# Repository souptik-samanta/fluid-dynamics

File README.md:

---
name: "Souptik Samanta"
slack_handle: "@Souptik Samanta"
github_handle: "@souptik-samanta"
tutorial: #no
wokwi: https://wokwi.com/projects/429317036413027329
---

# FLuid Dynamics

Wokwi link: https://wokwi.com/projects/429317036413027329

Led matrix pcb with rp2040 embeded into pcb to simulate fuild behavours based on inbuilt imu 

(pls include rough pricing of any extra components you're using 

| QTY  | PART                              | Approx Price | LCSC        |
|-----:|:----------------------------------|-------------:|:------------|
| 1    | IS31FL3741A-QFLS4-TR - 900Hz~29kHz 2.7V~5.5V QFN-60-EP(7x7) LED Drivers ICs ROHS | $2.89       | C2940604   |
| 5    | XDBS-CR2032-5 - Through Hole Blade Type Power Connector Assemblies ROHS | $0.30       | C48687404   |
| 2    | W25Q128JVSIQ - 128Mbit 2.7V~3.6V 133MHz SPI SOIC-8-208mil Memory (ICs) ROHS | $2.17       | C97521   |
| 5    | AMS1117-3.3 - 72dB@(120Hz) Positive SOT-223 Voltage Regulators - Linear, Low Drop Out (LDO) Regulators ROHS | $0.84       | C6186   |
| 1    | RP2040 - 133MHz LQFN-56(7x7) Microcontrollers ROHS | $1.14       | C2040   |
| 10   | SRV05-4 - 5A 75W 12.5V 6V Unidirectional SOT-23-6L TVS Diodes ROHS | $0.84       | C7420376   |
| 100  | FRC1206F2002TS - 250mW 20kΩ 200V ±100ppm/℃ Thick Film Resistor ±1% 1206 Chip Resistor - Surface Mount ROHS | $0.29       | C2933636   |
| 100  | 0402WGF274JTCE - 27.4Ω 62.5mW 50V ±100ppm/℃ Thick Film Resistor ±1% 0402 Chip Resistor - Surface Mount ROHS | $0.06       | C31439   |
| 100  | 0402WGF5101TCE - 5.1kΩ 62.5mW 50V ±100ppm/℃ Thick Film Resistor ±1% 0402 Chip Resistor - Surface Mount ROHS | $0.05       | C25905   |
| 100  | 0402WGF1001TCE - 1kΩ 62.5mW 50V ±100ppm/℃ Thick Film Resistor ±1% 0402 Chip Resistor - Surface Mount ROHS | $0.06       | C11702   |

final all toal is 20 - 25$ for parts  more parts on https://docs.google.com/spreadsheets/d/1B7IjNo7W825W_gv3a4BfWUKZrWtPnMB5DJiVofmm6nU/edit?usp=sharing

eh pretty easy

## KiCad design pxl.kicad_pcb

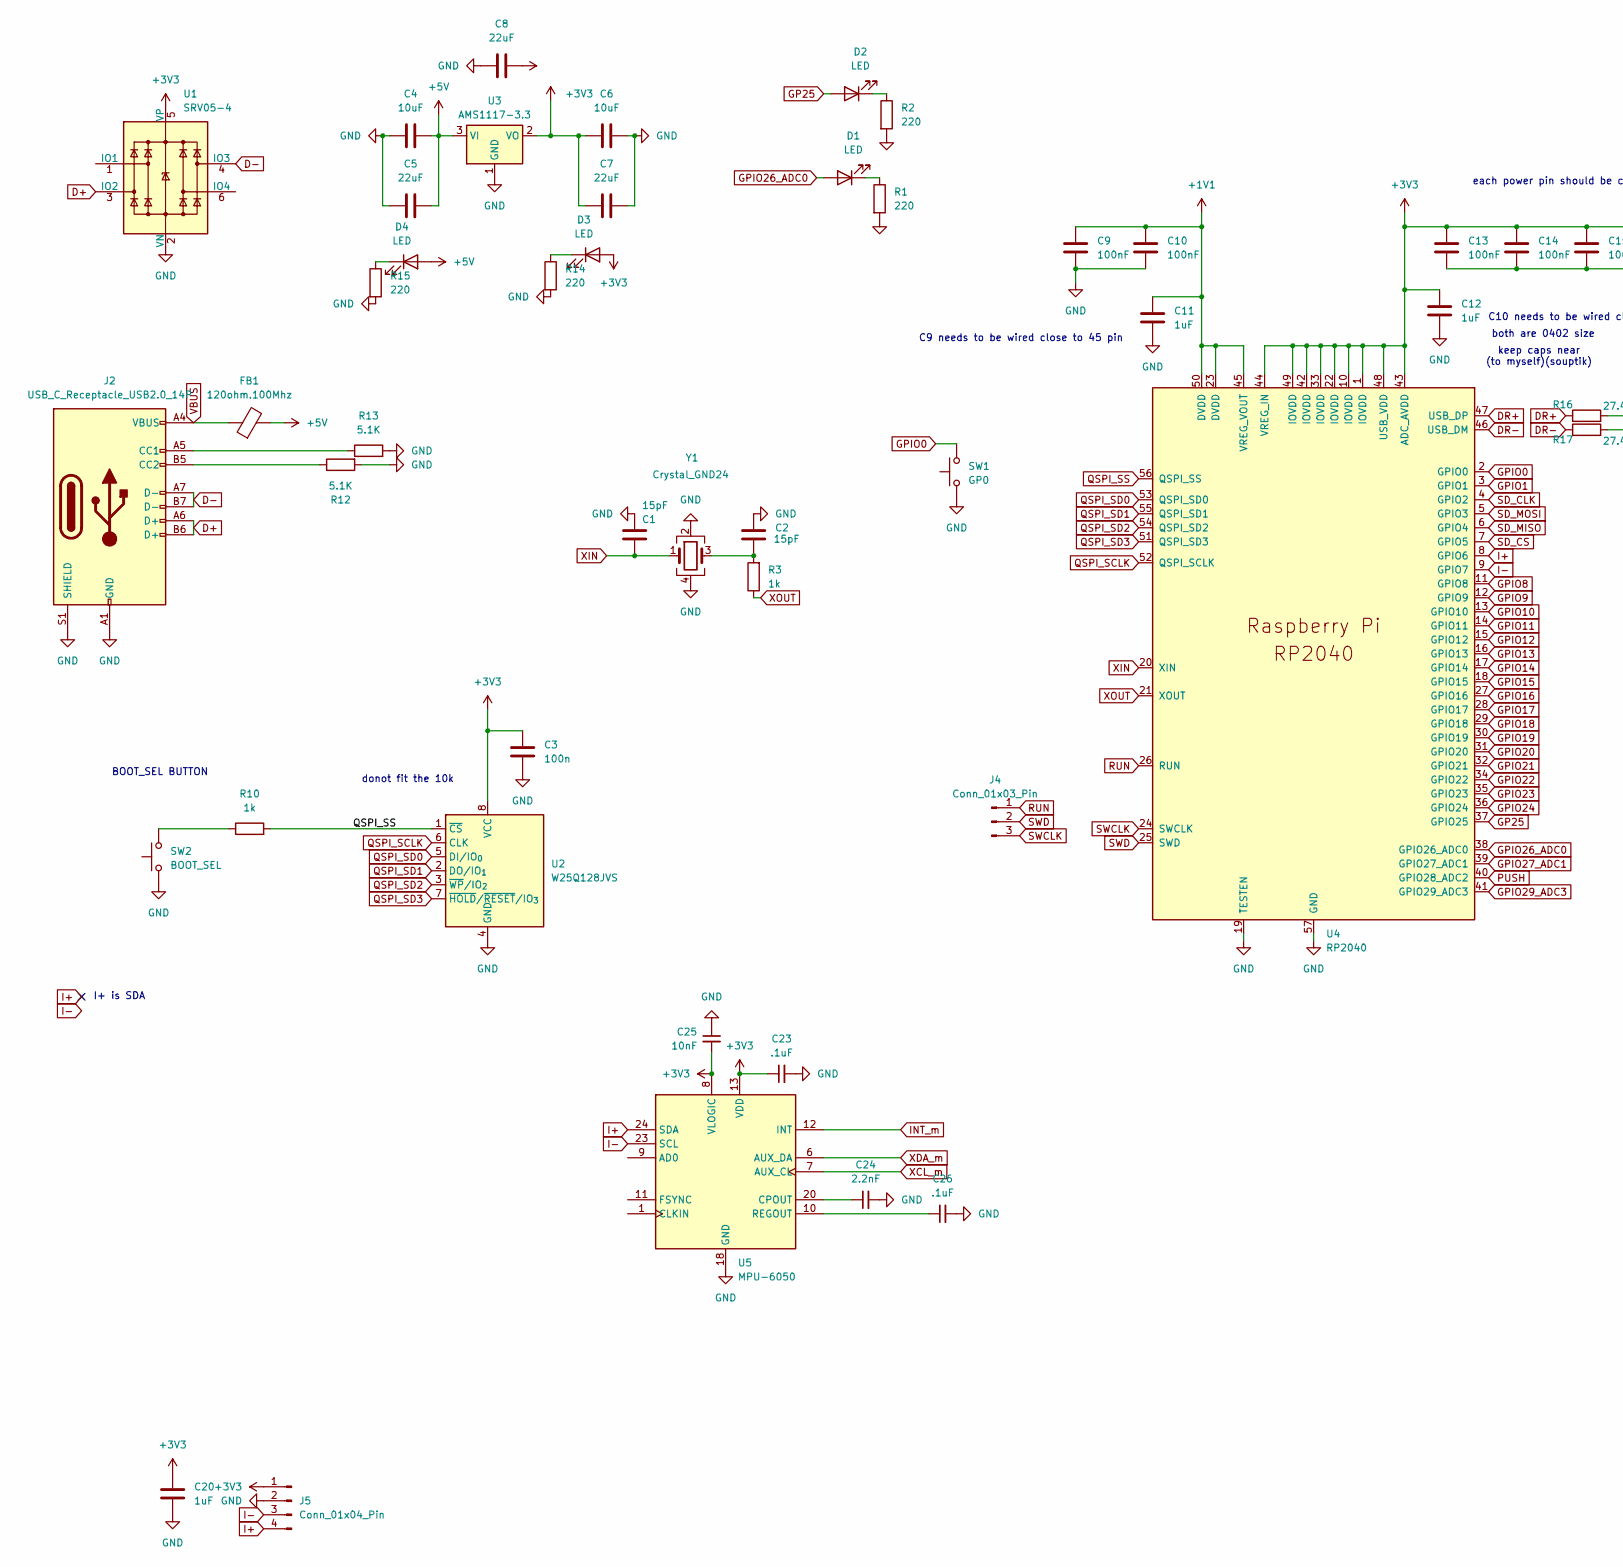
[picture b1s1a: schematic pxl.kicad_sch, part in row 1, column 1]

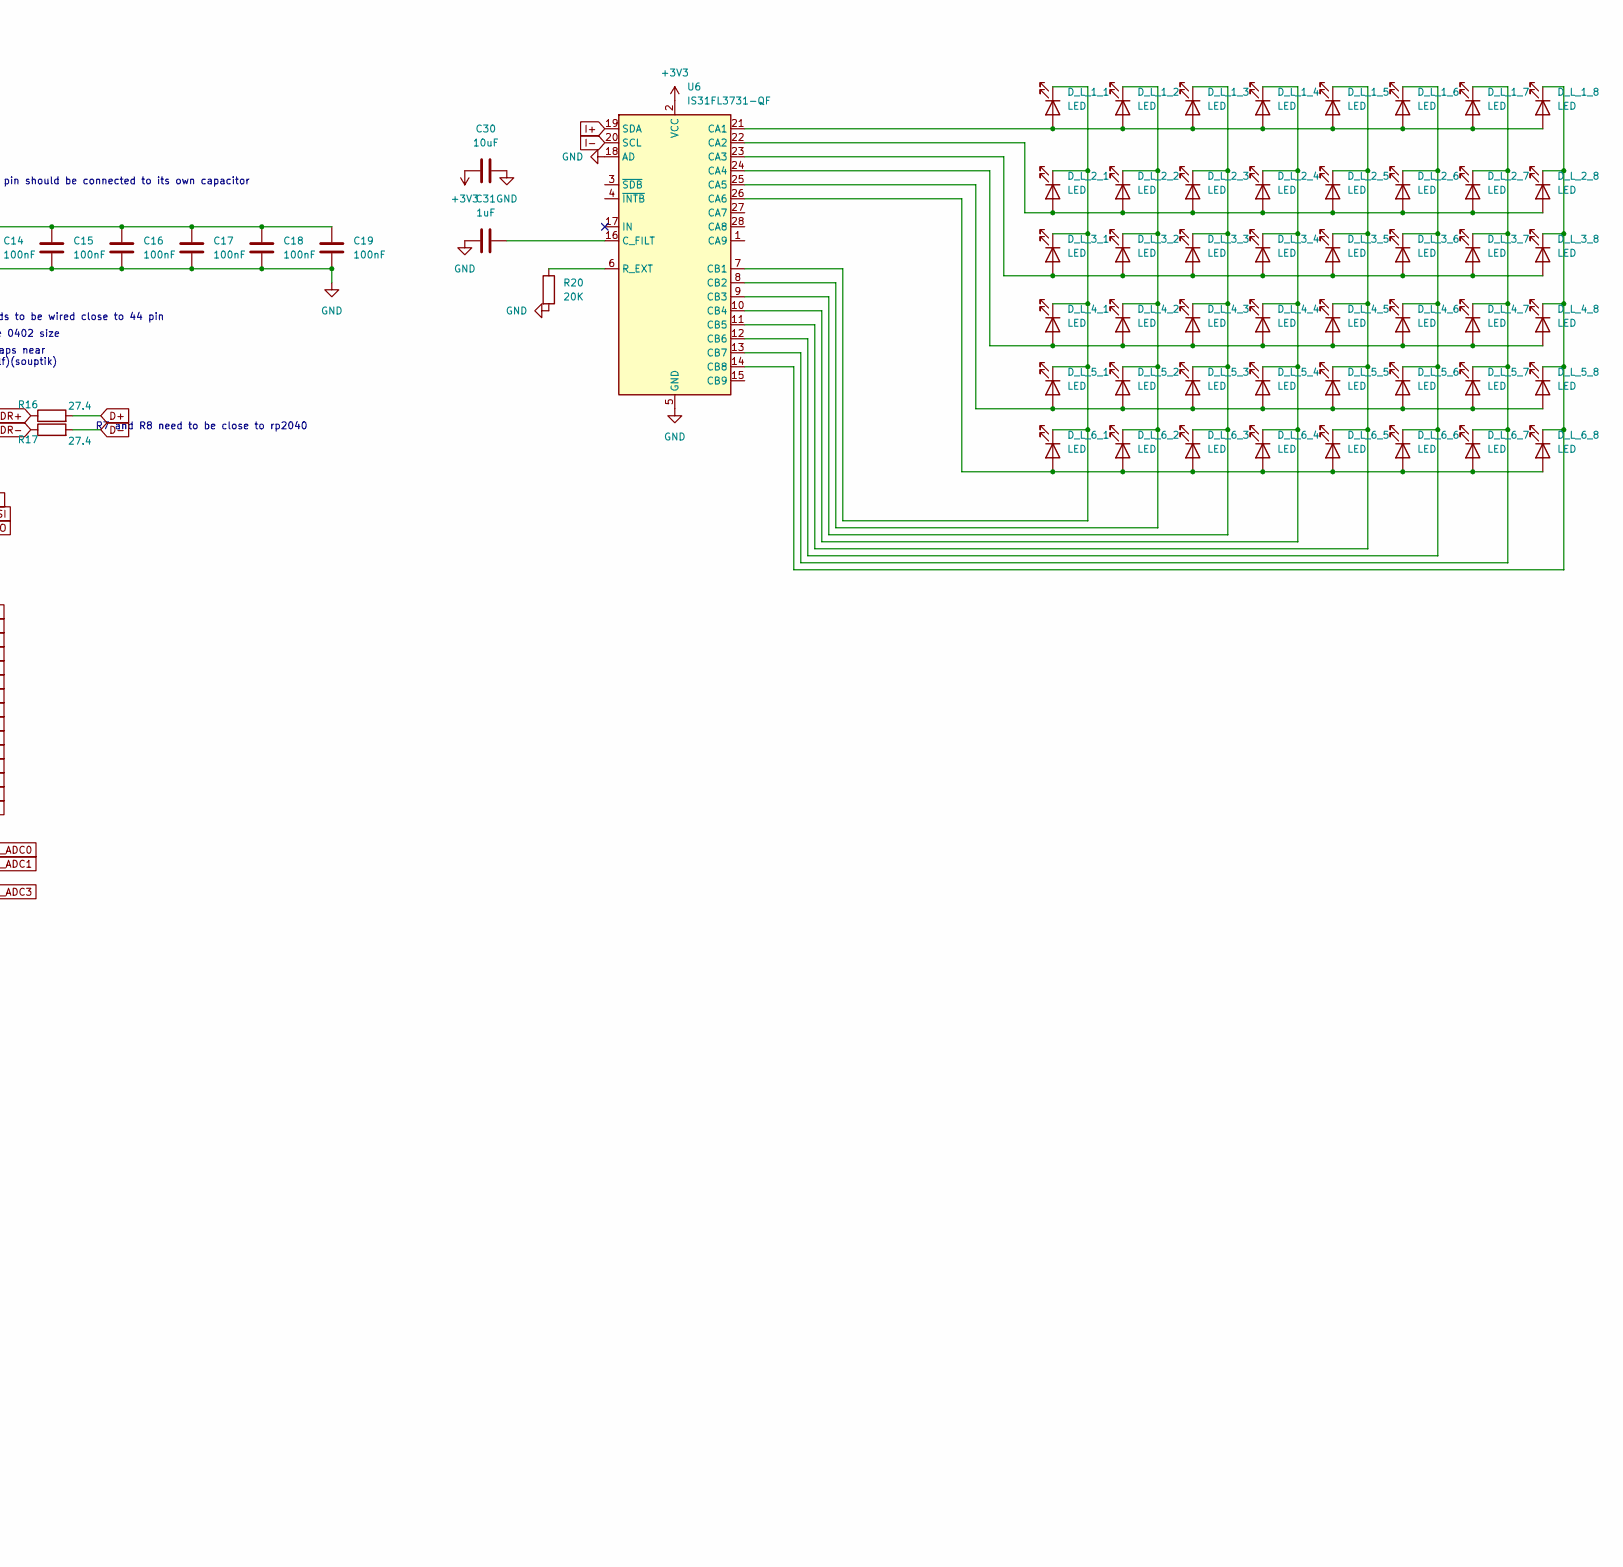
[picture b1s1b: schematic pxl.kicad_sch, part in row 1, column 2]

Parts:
C1, C2: 15pF; C_0402_1005Metric
C3: 100n; C_0402_1005Metric
C4, C6: 10uF; C_0603_1608Metric
C5, C7, C8: 22uF; C_0603_1608Metric
C9, C10, C13, C14, C15, C16, C17, C18, C19: 100nF; C_0402_1005Metric
C11, C12, C20: 1uF; C_0402_1005Metric
C23, C26: .1uF; C_0603_1608Metric_Pad1.08x0.95mm_HandSolder
C24: 2.2nF; C_0603_1608Metric_Pad1.08x0.95mm_HandSolder
C25: 10nF; C_0603_1608Metric_Pad1.08x0.95mm_HandSolder
C30: 10uF; C_0805_2012Metric
C31: 1uF; C_0805_2012Metric
D1, D2: LED; LED_0402_1005Metric
D3, D4: LED; LED_0603_1608Metric
D_L_1_1, D_L_1_2, D_L_1_3, D_L_1_4, D_L_1_5, D_L_1_6, D_L_1_7, D_L_1_8, D_L_2_1, D_L_2_2, D_L_2_3, D_L_2_4, D_L_2_5, D_L_2_6, D_L_2_7, D_L_2_8, D_L_3_1, D_L_3_2, D_L_3_3, D_L_3_4, D_L_3_5, D_L_3_6, D_L_3_7, D_L_3_8, D_L_4_1, D_L_4_2, D_L_4_3, D_L_4_4, D_L_4_5, D_L_4_6, D_L_4_7, D_L_4_8, D_L_5_1, D_L_5_2, D_L_5_3, D_L_5_4, D_L_5_5, D_L_5_6, D_L_5_7, D_L_5_8, D_L_6_1, D_L_6_2, D_L_6_3, D_L_6_4, D_L_6_5, D_L_6_6, D_L_6_7, D_L_6_8: LED; LED_0603_1608Metric
FB1: 120ohm.100Mhz; L_0805_2012Metric
J2: USB_C_Receptacle_USB2.0_14P; USB_C_Receptacle_HCTL_HC-TYPE-C-16P-01A
J4: Conn_01x03_Pin; PinHeader_1x03_P1.00mm_Vertical_SMD_Pin1Left
J5: Conn_01x04_Pin; PinHeader_1x04_P1.00mm_Vertical
R1, R2, R14, R15: 220; R_0402_1005Metric
R3, R10: 1k; R_0402_1005Metric
R12, R13: 5.1K; C_0402_1005Metric
R16, R17: 27.4; R_0402_1005Metric
R20: 20K; R_1206_3216Metric_Pad1.30x1.75mm_HandSolder
SW1: GP0; SW_Push_SPST_NO_Alps_SKRK; LCSC C318884
SW2: BOOT_SEL; SW_Push_SPST_NO_Alps_SKRK; LCSC C318884
U1: SRV05-4; SOT-23-6
U2: W25Q128JVS; SOIC-8_5.3x5.3mm_P1.27mm
U3: AMS1117-3.3; SOT-223-3_TabPin2
U4: RP2040; QFN-56-1EP_7x7mm_P0.4mm_EP3.2x3.2mm
U5: MPU-6050; InvenSense_QFN-24_4x4mm_P0.5mm
U6: IS31FL3731-QF; QFN-28-1EP_4x4mm_P0.4mm_EP2.4x2.4mm_ThermalVias
Y1: Crystal_GND24; Crystal_SMD_Abracon_ABM8G-4Pin_3.2x2.5mm

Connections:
+1V1: C9.1, C10.1, C11.1, U4.23 (DVDD), U4.45 (VREG_VOUT), U4.50 (DVDD)
+3V3: C3.1, C6.2, C7.2, C12.1, C13.1, C14.1, C15.1, C16.1, C17.1, C18.1, C19.1, C20.1, C23.1, C25.2, C30.2, D3.2 (A), J5.1, U1.5 (VP), U2.8 (VCC), U3.2 (VO), U4.1 (IOVDD), U4.10 (IOVDD), U4.22 (IOVDD), U4.33 (IOVDD), U4.42 (IOVDD), U4.43 (ADC_AVDD), U4.44 (VREG_IN), U4.48 (USB_VDD), U4.49 (IOVDD), U5.8 (VLOGIC), U5.13 (VDD), U6.2 (VCC)
+5V: C4.1, C5.1, C8.1, D4.2 (A), FB1.2, U3.3 (VI)
D+: J2.A6 (D+), J2.B6 (D+), R16.2, U1.3 (IO2)
D-: J2.A7 (D-), J2.B7 (D-), R17.2, U1.4 (IO3)
DR+: R16.1, U4.47 (USB_DP)
DR-: R17.1, U4.46 (USB_DM)
GND: C1.2, C2.2, C3.2, C4.2, C5.2, C6.1, C7.1, C8.2, C9.2, C10.2, C11.2, C12.2, C13.2, C14.2, C15.2, C16.2, C17.2, C18.2, C19.2, C20.2, C23.2, C24.2, C25.1, C26.2, C30.1, C31.2, J2.A1 (GND), J2.A12 (GND), J2.B1 (GND), J2.B12 (GND), J2.S1 (SHIELD), J5.2, R1.2, R2.2, R12.2, R13.2, R14.2, R15.2, R20.2, SW1.1, SW2.1, U1.2 (VN), U2.4 (GND), U3.1 (GND), U4.19 (TESTEN), U4.57 (GND), U5.18 (GND), U6.5 (GND), U6.18 (AD), U6.29 (GND), Y1.2, Y1.4
GP25: D2.2 (A), U4.37 (GPIO25)
GPIO0: SW1.2, U4.2 (GPIO0)
GPIO1: U4.3 (GPIO1)
GPIO8: U4.11 (GPIO8)
GPIO9: U4.12 (GPIO9)
GPIO10: U4.13 (GPIO10)
GPIO11: U4.14 (GPIO11)
GPIO12: U4.15 (GPIO12)
GPIO13: U4.16 (GPIO13)
GPIO14: U4.17 (GPIO14)
GPIO15: U4.18 (GPIO15)
GPIO16: U4.27 (GPIO16)
GPIO17: U4.28 (GPIO17)
GPIO18: U4.29 (GPIO18)
GPIO19: U4.30 (GPIO19)
GPIO20: U4.31 (GPIO20)
GPIO21: U4.32 (GPIO21)
GPIO22: U4.34 (GPIO22)
GPIO23: U4.35 (GPIO23)
GPIO24: U4.36 (GPIO24)
GPIO26_ADC0: D1.2 (A), U4.38 (GPIO26_ADC0)
GPIO27_ADC1: U4.39 (GPIO27_ADC1)
GPIO29_ADC3: U4.41 (GPIO29_ADC3)
I+: J5.4, U4.8 (GPIO6), U5.24 (SDA), U6.19 (SDA)
I-: J5.3, U4.9 (GPIO7), U5.23 (SCL), U6.20 (SCL)
INT_m: U5.12 (INT)
unnamed: C2.1, R3.2, Y1.3
unnamed: D1.1 (K), R1.1
unnamed: D2.1 (K), R2.1
unnamed: D3.1 (K), R14.1
unnamed: D4.1 (K), R15.1
unnamed: D_L_1_1.2 (A), D_L_1_2.2 (A), D_L_1_3.2 (A), D_L_1_4.2 (A), D_L_1_5.2 (A), D_L_1_6.2 (A), D_L_1_7.2 (A), D_L_1_8.2 (A), U6.21 (CA1)
unnamed: D_L_1_1.1 (K), D_L_2_1.1 (K), D_L_3_1.1 (K), D_L_4_1.1 (K), D_L_5_1.1 (K), D_L_6_1.1 (K), U6.7 (CB1)
unnamed: D_L_1_2.1 (K), D_L_2_2.1 (K), D_L_3_2.1 (K), D_L_4_2.1 (K), D_L_5_2.1 (K), D_L_6_2.1 (K), U6.8 (CB2)
unnamed: D_L_1_3.1 (K), D_L_2_3.1 (K), D_L_3_3.1 (K), D_L_4_3.1 (K), D_L_5_3.1 (K), D_L_6_3.1 (K), U6.9 (CB3)
unnamed: D_L_1_4.1 (K), D_L_2_4.1 (K), D_L_3_4.1 (K), D_L_4_4.1 (K), D_L_5_4.1 (K), D_L_6_4.1 (K), U6.10 (CB4)
unnamed: D_L_1_5.1 (K), D_L_2_5.1 (K), D_L_3_5.1 (K), D_L_4_5.1 (K), D_L_5_5.1 (K), D_L_6_5.1 (K), U6.11 (CB5)
unnamed: D_L_1_6.1 (K), D_L_2_6.1 (K), D_L_3_6.1 (K), D_L_4_6.1 (K), D_L_5_6.1 (K), D_L_6_6.1 (K), U6.12 (CB6)
unnamed: D_L_1_7.1 (K), D_L_2_7.1 (K), D_L_3_7.1 (K), D_L_4_7.1 (K), D_L_5_7.1 (K), D_L_6_7.1 (K), U6.13 (CB7)
unnamed: D_L_1_8.1 (K), D_L_2_8.1 (K), D_L_3_8.1 (K), D_L_4_8.1 (K), D_L_5_8.1 (K), D_L_6_8.1 (K), U6.14 (CB8)
unnamed: D_L_2_1.2 (A), D_L_2_2.2 (A), D_L_2_3.2 (A), D_L_2_4.2 (A), D_L_2_5.2 (A), D_L_2_6.2 (A), D_L_2_7.2 (A), D_L_2_8.2 (A), U6.22 (CA2)
unnamed: D_L_3_1.2 (A), D_L_3_2.2 (A), D_L_3_3.2 (A), D_L_3_4.2 (A), D_L_3_5.2 (A), D_L_3_6.2 (A), D_L_3_7.2 (A), D_L_3_8.2 (A), U6.23 (CA3)
unnamed: D_L_4_1.2 (A), D_L_4_2.2 (A), D_L_4_3.2 (A), D_L_4_4.2 (A), D_L_4_5.2 (A), D_L_4_6.2 (A), D_L_4_7.2 (A), D_L_4_8.2 (A), U6.24 (CA4)
unnamed: D_L_5_1.2 (A), D_L_5_2.2 (A), D_L_5_3.2 (A), D_L_5_4.2 (A), D_L_5_5.2 (A), D_L_5_6.2 (A), D_L_5_7.2 (A), D_L_5_8.2 (A), U6.25 (CA5)
unnamed: D_L_6_1.2 (A), D_L_6_2.2 (A), D_L_6_3.2 (A), D_L_6_4.2 (A), D_L_6_5.2 (A), D_L_6_6.2 (A), D_L_6_7.2 (A), D_L_6_8.2 (A), U6.26 (CA6)
unnamed: J2.A5 (CC1), R13.1
unnamed: J2.B5 (CC2), R12.1
unnamed: R10.1, SW2.2
unnamed: C24.1, U5.20 (CPOUT)
unnamed: C26.1, U5.10 (REGOUT)
unnamed: C31.1, U6.16 (C_FILT)
unnamed: R20.1, U6.6 (R_EXT)
PUSH: U4.40 (GPIO28_ADC2)
QSPI_SCLK: U2.6 (CLK), U4.52 (QSPI_SCLK)
QSPI_SD0: U2.5 (DI/IO_{0}), U4.53 (QSPI_SD0)
QSPI_SD1: U2.2 (DO/IO_{1}), U4.55 (QSPI_SD1)
QSPI_SD2: U2.3 (~WP/IO_{2}), U4.54 (QSPI_SD2)
QSPI_SD3: U2.7 (~HOLD/~RESET/IO_{3}), U4.51 (QSPI_SD3)
QSPI_SS: R10.2, U2.1 (~CS), U4.56 (QSPI_SS)
RUN: J4.1, U4.26 (RUN)
SD_CLK: U4.4 (GPIO2)
SD_CS: U4.7 (GPIO5)
SD_MISO: U4.6 (GPIO4)
SD_MOSI: U4.5 (GPIO3)
SWCLK: J4.3, U4.24 (SWCLK)
SWD: J4.2, U4.25 (SWD)
VBUS: FB1.1, J2.A4 (VBUS), J2.A9 (VBUS), J2.B4 (VBUS), J2.B9 (VBUS)
XCL_m: U5.7 (AUX_CL)
XDA_m: U5.6 (AUX_DA)
XIN: C1.1, U4.20 (XIN), Y1.1
XOUT: R3.1, U4.21 (XOUT)

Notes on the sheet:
each power pin should be connected to its own capacitor
keep caps near (to myself)(souptik)
C9 needs to be wired close to 45 pin
donot fit the 10k
both are 0402 size
R7 and R8 need to be close to rp2040
I+ is SDA
BOOT_SEL BUTTON
C10 needs to be wired close to 44 pin

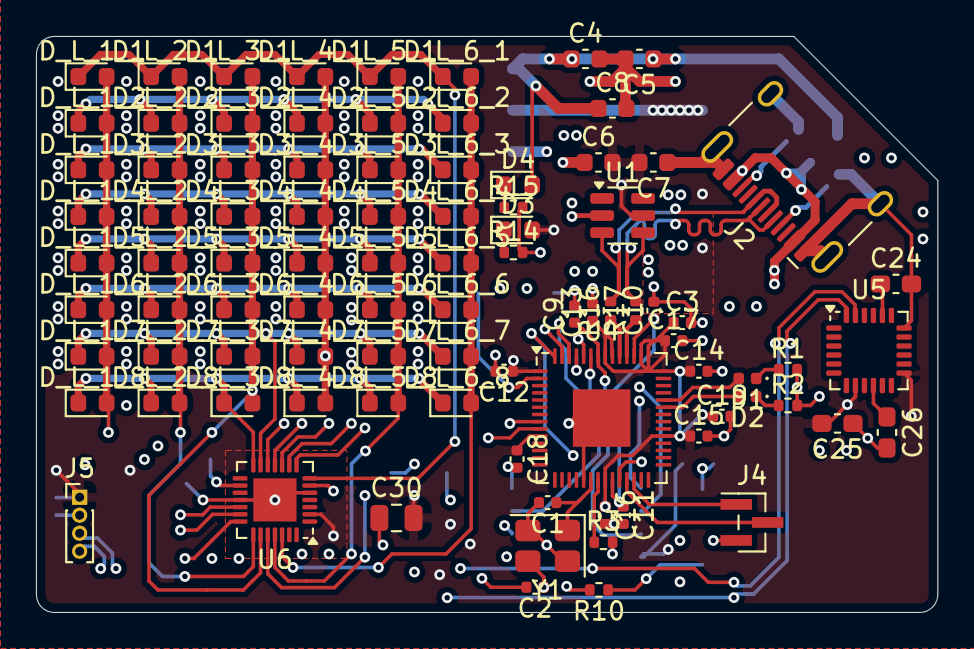
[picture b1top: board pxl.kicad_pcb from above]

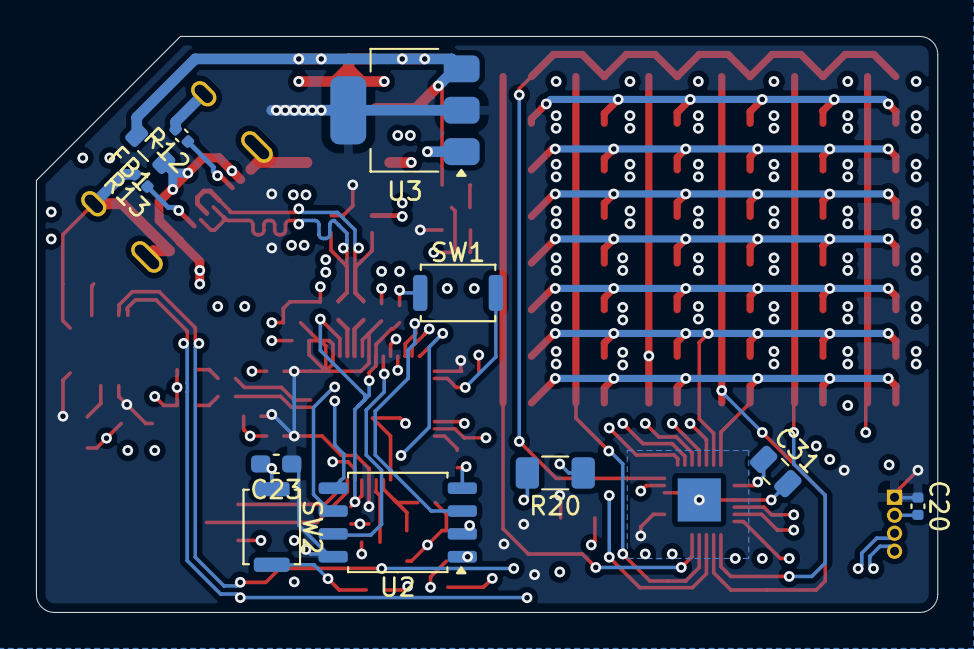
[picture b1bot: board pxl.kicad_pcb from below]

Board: 4 copper layers, 50.1 x 32.0 mm, 102 parts (11 on the bottom side), 51 nets.

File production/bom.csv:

Designator,Footprint,Quantity,Value,LCSC Part #
"C1, C2",0402,2,15pF,
"C10, C13, C14, C15, C16, C17, C18, C19, C9",0402,9,100nF,
"C11, C12, C20",0402,3,1uF,
"C23, C26",0603,2,.1uF,
C24,0603,1,2.2nF,
C25,0603,1,10nF,
C3,0402,1,100n,
C30,0805,1,10uF,
C31,0805,1,1uF,
"C4, C6",0603,2,10uF,
"C5, C7, C8",0603,3,22uF,
"D1, D2",0402,2,LED,
"D3, D4, D_L_1_1, D_L_1_2, D_L_1_3, D_L_1_4, D_L_1_5, D_L_1_6, D_L_1_7, D_L_1_8, D_L_2_1, D_L_2_2, D_L_2_3, D_L_2_4, D_L_2_5, D_L_2_6, D_L_2_7, D_L_2_8, D_L_3_1, D_L_3_2, D_L_3_3, D_L_3_4, D_L_3_5, D_L_3_6, D_L_3_7, D_L_3_8, D_L_4_1, D_L_4_2, D_L_4_3, D_L_4_4, D_L_4_5, D_L_4_6, D_L_4_7, D_L_4_8, D_L_5_1, D_L_5_2, D_L_5_3, D_L_5_4, D_L_5_5, D_L_5_6, D_L_5_7, D_L_5_8, D_L_6_1, D_L_6_2, D_L_6_3, D_L_6_4, D_L_6_5, D_L_6_6, D_L_6_7, D_L_6_8",0603,50,LED,
FB1,0805,1,120ohm.100Mhz,
J2,USB_C_Receptacle_HCTL_HC-TYPE-C-16P-01A,1,USB_C_Receptacle_USB2.0_14P,
J4,PinHeader_1x03_P1.00mm_Vertical_SMD_Pin1Left,1,Conn_01x03_Pin,
J5,PinHeader_1x04_P1.00mm_Vertical,1,Conn_01x04_Pin,
"R1, R14, R15, R2",0402,4,220,
"R10, R3",0402,2,1k,
"R12, R13",0402,2,5.1K,
"R16, R17",0402,2,27.4,
R20,1206,1,20K,
SW1,SW_Push_SPST_NO_Alps_SKRK,1,GP0,C318884
SW2,SW_Push_SPST_NO_Alps_SKRK,1,BOOT_SEL,C318884
U1,SOT-23-6,1,SRV05-4,
U2,SOIC-8_5.3x5.3mm_P1.27mm,1,W25Q128JVS,
U3,SOT-223-3_TabPin2,1,AMS1117-3.3,
U4,QFN-56-1EP_7x7mm_P0.4mm_EP3.2x3.2mm,1,RP2040,
U5,InvenSense_QFN-24_4x4mm_P0.5mm,1,MPU-6050,
U6,QFN-28-1EP_4x4mm_P0.4mm_EP2.4x2.4mm_ThermalVias,1,IS31FL3731-QF,
Y1,Crystal_SMD_Abracon_ABM8G-4Pin_3.2x2.5mm,1,Crystal_GND24,
